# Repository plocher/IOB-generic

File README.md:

# IOB-Generic
## License: CERN Open Hardware Licence v1.2

IOB interface provides 1x IO4 port with 4x generic (hardwired) Input or Output i/o lines.

  * An optional series resistor can be used to current limit directly connected LEDs

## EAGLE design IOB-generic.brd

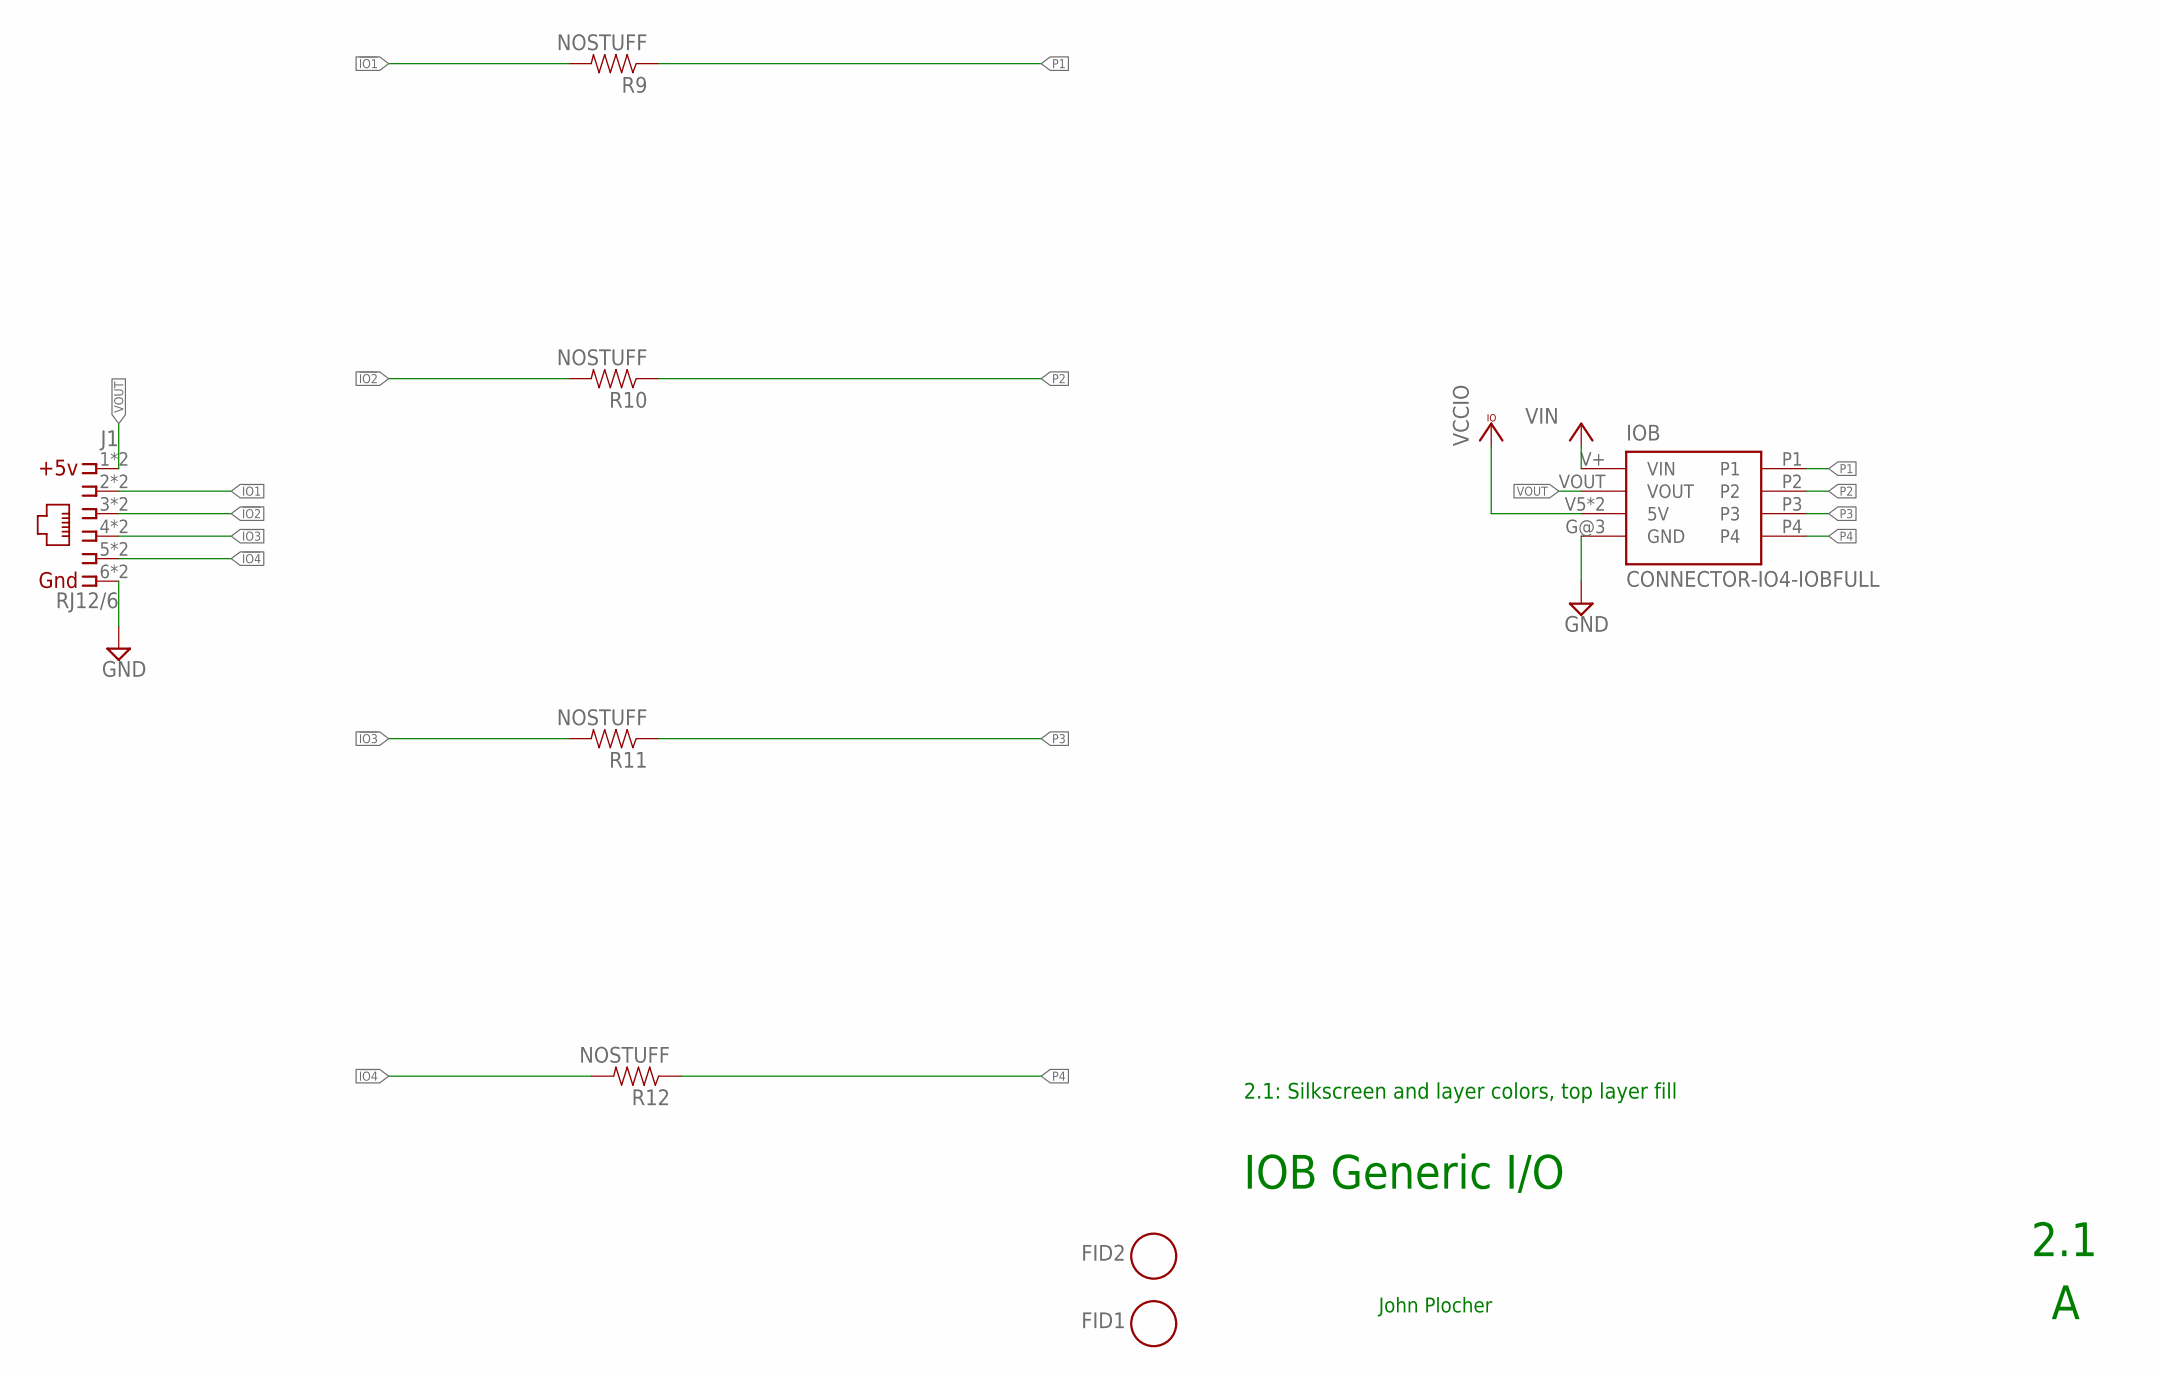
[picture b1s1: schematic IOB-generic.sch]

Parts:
FID1, FID2: FIDUCIAL; FIDUCIAL_1MM
IOB: CONNECTOR-IO4-IOBFULL; IO4-IOB
J1: RJ12/6; RJ24-INVERTED-PINS
R9, R10, R11, R12: NOSTUFF; AXIAL-0.4-RES

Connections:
!IO1: J1.2, J1.2@1 (2), R9.P$2 (2)
!IO2: J1.3, J1.3@1 (3), R10.P$2 (2)
!IO3: J1.4, J1.4@1 (4), R11.P$2 (2)
!IO4: J1.5, J1.5@1 (5), R12.P$2 (2)
GND: IOB.G@3 (GND), J1.6, J1.6@1 (6)
P1: IOB.P1, R9.P$1 (1)
P2: IOB.P2, R10.P$1 (1)
P3: IOB.P3, R11.P$1 (1)
P4: IOB.P4, R12.P$1 (1)
VCCIO: IOB.V5 (5V), IOB.V5@1 (5V)
VIN: IOB.V+ (VIN)
VOUT: IOB.VOUT, J1.1, J1.1@1 (1)

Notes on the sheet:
IOB Generic I/O
2.1
John Plocher
2.1: Silkscreen and layer colors, top layer fill

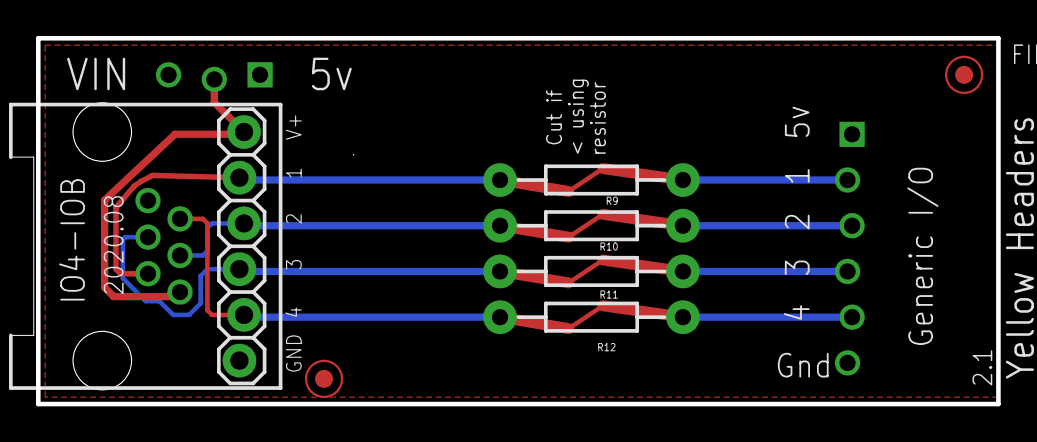
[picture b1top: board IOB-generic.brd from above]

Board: 2 copper layers, 53.3 x 20.3 mm, 8 parts (0 on the bottom side), 11 nets.

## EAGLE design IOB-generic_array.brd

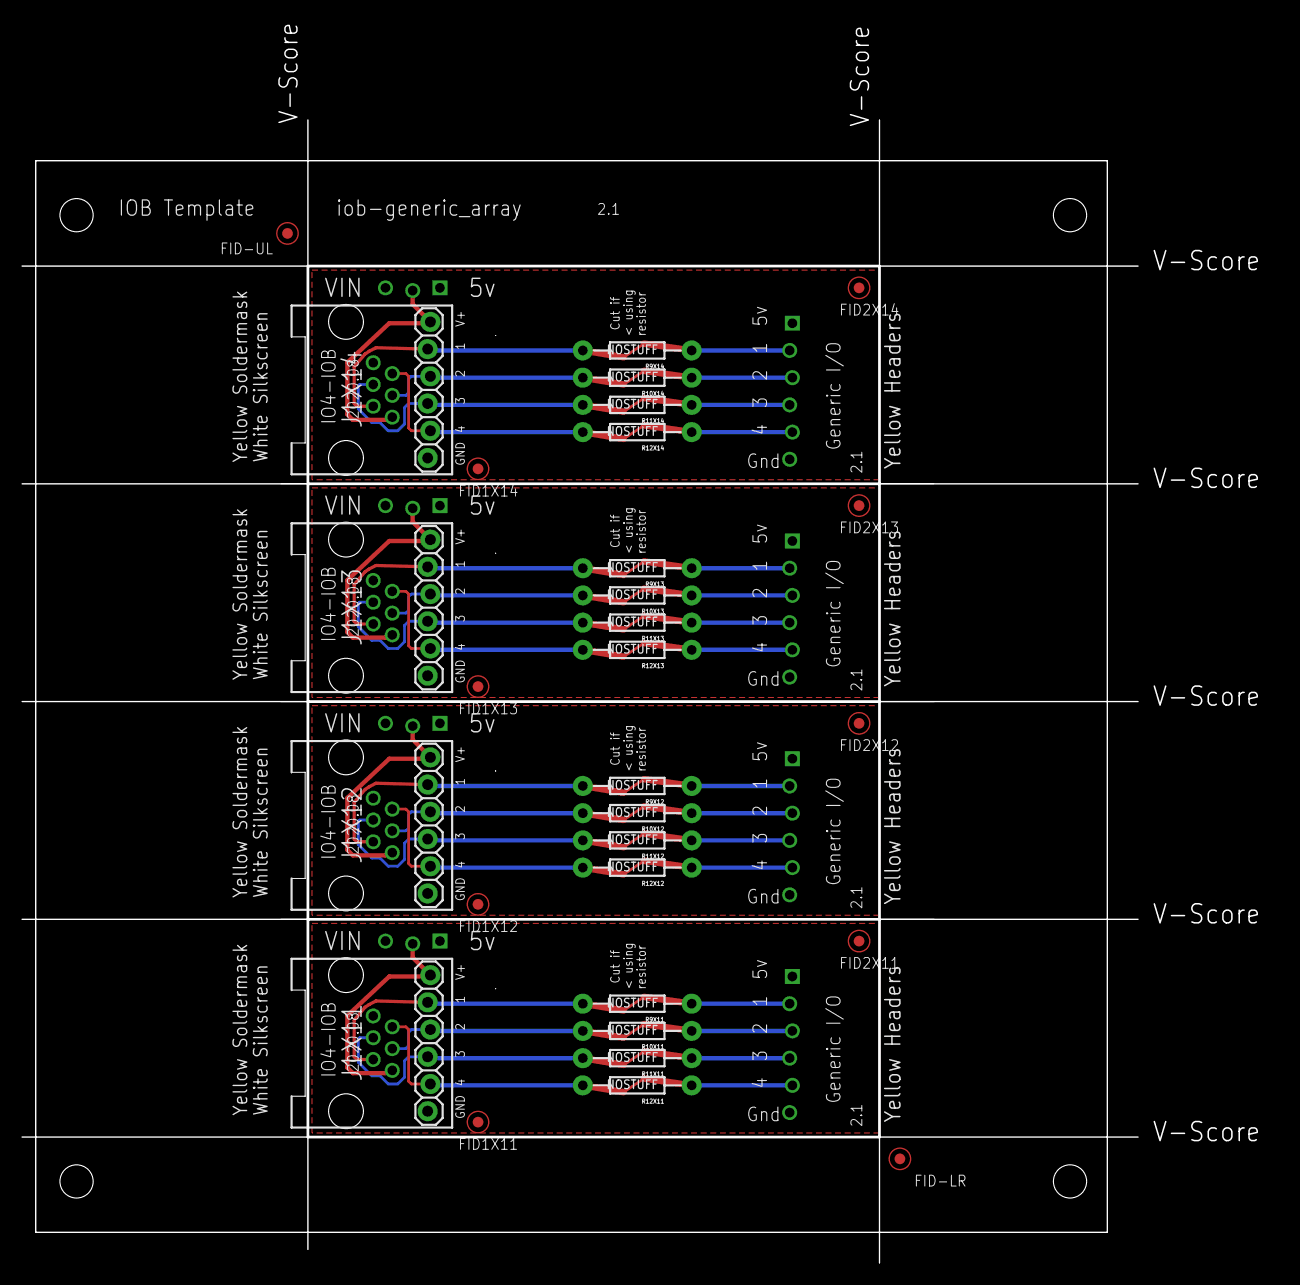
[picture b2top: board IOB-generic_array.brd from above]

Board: 2 copper layers, 117.1 x 115.7 mm, 35 parts (0 on the bottom side), 44 nets.

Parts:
FID1X11, FID1X12, FID1X13, FID1X14, FID2X11, FID2X12, FID2X13, FID2X14: FIDUCIAL; FIDUCIAL_1MM
FID-LR: FIDUCIAL; FIDUCIAL_1MM
FID-UL: FIDUCIAL; FIDUCIAL_1MM
IOBX11, IOBX12, IOBX13, IOBX14: CONNECTOR-IO4-IOBFULL; IO4-IOB
J1X11, J1X12, J1X13, J1X14: RJ12/6; RJ24-INVERTED-PINS
R9X11, R9X12, R9X13, R9X14, R10X11, R10X12, R10X13, R10X14, R11X11, R11X12, R11X13, R11X14, R12X11, R12X12, R12X13, R12X14: NOSTUFF; AXIAL-0.4-RES
R12X1: BOARD-DINRAIL-3.17IN-H4X-IOB

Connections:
!IO1X11: J1X11.2, J1X11.2@1, R9X11.P$2
!IO1X12: J1X12.2, J1X12.2@1, R9X12.P$2
!IO1X13: J1X13.2, J1X13.2@1, R9X13.P$2
!IO1X14: J1X14.2, J1X14.2@1, R9X14.P$2
!IO2X11: J1X11.3, J1X11.3@1, R10X11.P$2
!IO2X12: J1X12.3, J1X12.3@1, R10X12.P$2
!IO2X13: J1X13.3, J1X13.3@1, R10X13.P$2
!IO2X14: J1X14.3, J1X14.3@1, R10X14.P$2
!IO3X11: J1X11.4, J1X11.4@1, R11X11.P$2
!IO3X12: J1X12.4, J1X12.4@1, R11X12.P$2
!IO3X13: J1X13.4, J1X13.4@1, R11X13.P$2
!IO3X14: J1X14.4, J1X14.4@1, R11X14.P$2
!IO4X11: J1X11.5, J1X11.5@1, R12X11.P$2
!IO4X12: J1X12.5, J1X12.5@1, R12X12.P$2
!IO4X13: J1X13.5, J1X13.5@1, R12X13.P$2
!IO4X14: J1X14.5, J1X14.5@1, R12X14.P$2
GNDX11: IOBX11.G@3, J1X11.6, J1X11.6@1
GNDX12: IOBX12.G@3, J1X12.6, J1X12.6@1
GNDX13: IOBX13.G@3, J1X13.6, J1X13.6@1
GNDX14: IOBX14.G@3, J1X14.6, J1X14.6@1
P1X11: IOBX11.P1, R9X11.P$1
P1X12: IOBX12.P1, R9X12.P$1
P1X13: IOBX13.P1, R9X13.P$1
P1X14: IOBX14.P1, R9X14.P$1
P2X11: IOBX11.P2, R10X11.P$1
P2X12: IOBX12.P2, R10X12.P$1
P2X13: IOBX13.P2, R10X13.P$1
P2X14: IOBX14.P2, R10X14.P$1
P3X11: IOBX11.P3, R11X11.P$1
P3X12: IOBX12.P3, R11X12.P$1
P3X13: IOBX13.P3, R11X13.P$1
P3X14: IOBX14.P3, R11X14.P$1
P4X11: IOBX11.P4, R12X11.P$1
P4X12: IOBX12.P4, R12X12.P$1
P4X13: IOBX13.P4, R12X13.P$1
P4X14: IOBX14.P4, R12X14.P$1
VCCIOX11: IOBX11.V5, IOBX11.V5@1
VCCIOX12: IOBX12.V5, IOBX12.V5@1
VCCIOX13: IOBX13.V5, IOBX13.V5@1
VCCIOX14: IOBX14.V5, IOBX14.V5@1
VOUTX11: IOBX11.VOUT, J1X11.1, J1X11.1@1
VOUTX12: IOBX12.VOUT, J1X12.1, J1X12.1@1
VOUTX13: IOBX13.VOUT, J1X13.1, J1X13.1@1
VOUTX14: IOBX14.VOUT, J1X14.1, J1X14.1@1

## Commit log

2020-01-25 Generic I/O IOB
2020-03-04 NEW IOB form factor
2020-03-04 generated new array
2020-03-04 added array...
2020-03-07 updated changelog
2020-04-15 updated to use SPCoast colors and layers
2020-05-04 updated tags
2020-05-04 updated version number
2020-08-09 silkscreen and top fill
2020-08-09 silkscreen and top fill, array
2020-08-09 Fab Date, DRC
2020-08-09 Fab date, keepout, DRC
2020-08-09 Gen Array
2020-08-11 normalized silkscreen layout across IOBs
2020-08-11 move text from DOCU to TPLACE
2020-08-11 SPCoast Color Pallette
